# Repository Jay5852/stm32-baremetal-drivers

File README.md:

# STM32 Bare-Metal Driver Development & Custom PCB Design

## 📌 Overview

This project demonstrates low-level embedded systems development using STM32 microcontrollers.

## 🚀 Features

- UART Driver (Polling, Interrupt, DMA)
- ADC Driver (Polling + DMA)
- Timer-triggered ADC sampling
- Custom STM32 PCB Design

## 🧠 Key Concepts

- Register-level programming
- RCC configuration
- Interrupt handling (NVIC)
- DMA optimization
- Power design and decoupling

## 🛠 Tools Used

- STM32CubeIDE
- KiCad
- Git & GitHub

## 📌 Author

Jay Dukare

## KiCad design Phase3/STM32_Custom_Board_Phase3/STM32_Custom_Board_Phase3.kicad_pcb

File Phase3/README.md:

# STM32 Custom Board Project

## Overview
A custom STM32F401 breakout board designed for student lab use.

## Contents
- /gerber_files: Manufacturing data (Gerber + Drill).
- /layout_pdfs: PDF visual guides.
- schematic.pdf: Circuit diagram.

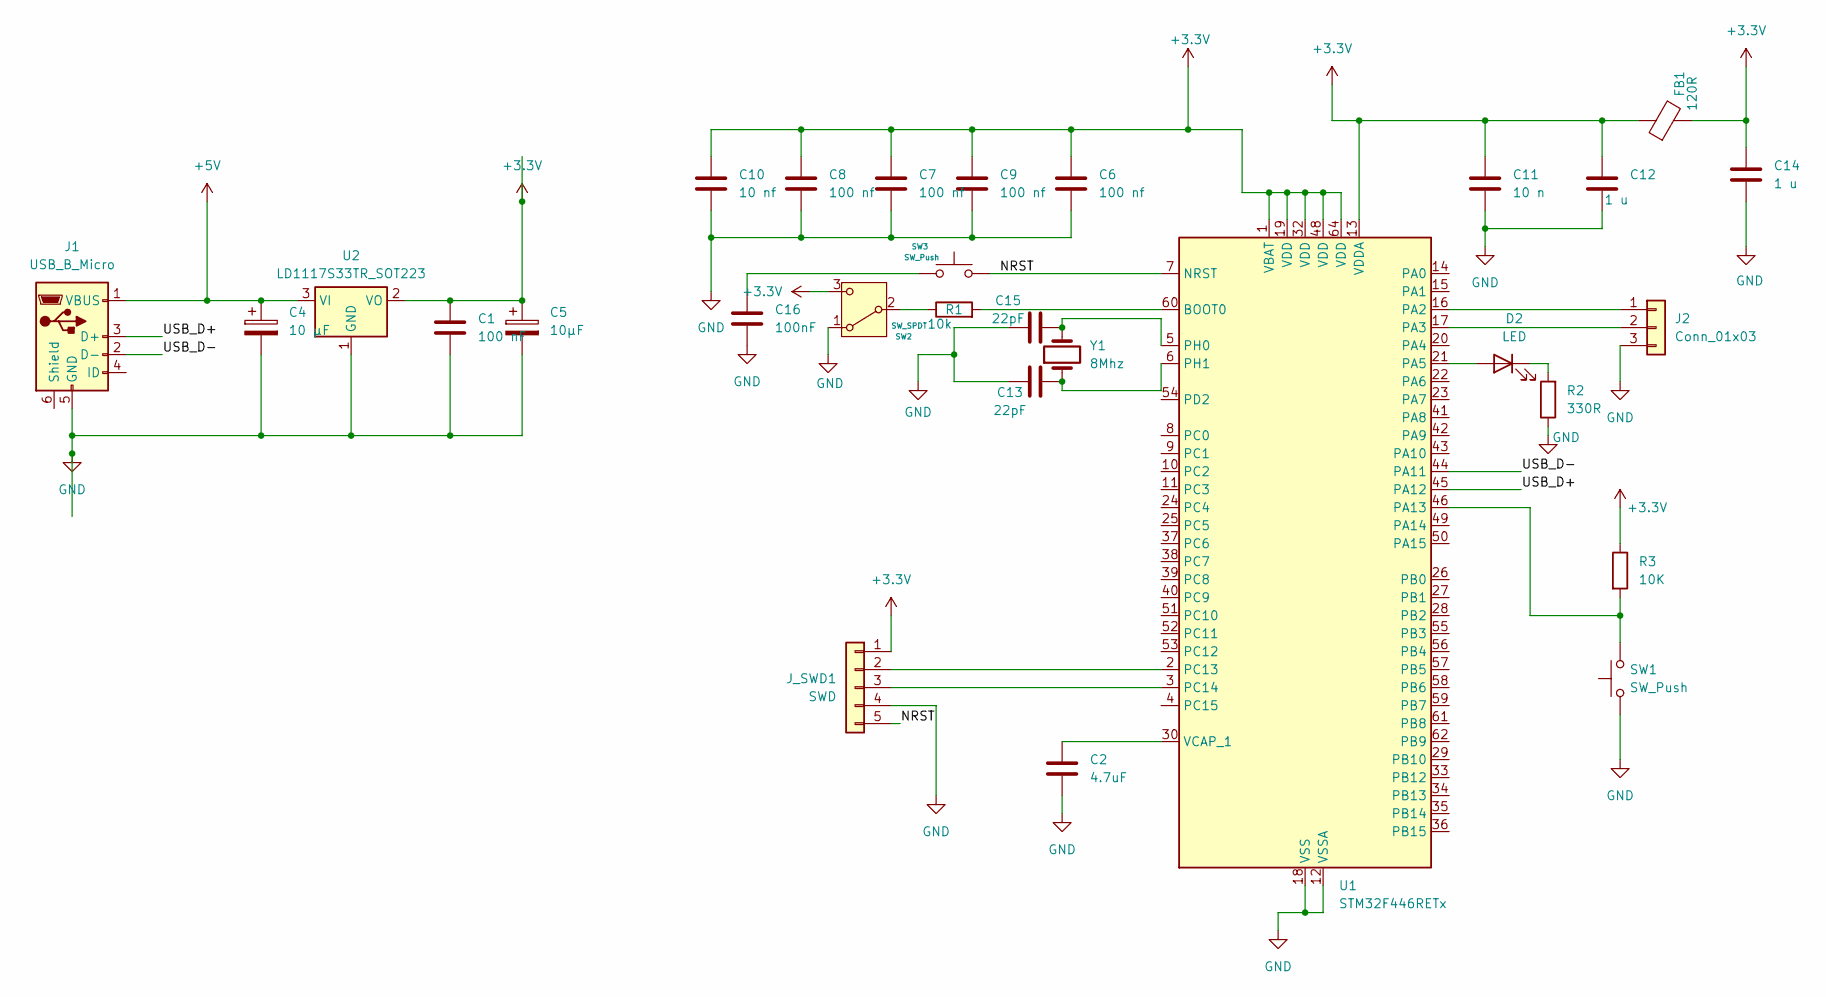
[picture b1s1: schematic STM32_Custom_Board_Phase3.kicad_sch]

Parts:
C1: 100 nF; C_0603_1608Metric
C2: 4.7uF; C_0603_1608Metric
C4: 10 µF; C_0603_1608Metric
C5: 10µF; C_0603_1608Metric
C6, C7, C8, C9: 100 nf; C_0603_1608Metric
C10: 10 nf; C_0603_1608Metric
C11: 10 n; C_0603_1608Metric
C12, C14: 1 u; C_0603_1608Metric
C13, C15: 22pF; C_0603_1608Metric
C16: 100nF; C_0603_1608Metric
D2: LED; LED_0603_1608Metric
FB1: 120R; L_0603_1608Metric
J1: USB_B_Micro; USB_Micro-B_Molex-105017-0001
J2: Conn_01x03; PinHeader_1x03_P2.54mm_Vertical
J_SWD1: SWD; PinHeader_1x05_P2.54mm_Vertical
R1: 10k; R_0603_1608Metric
R2: 330R; R_0603_1608Metric
R3: 10K; R_0603_1608Metric
SW1, SW3: SW_Push; SW_Push_1TS009xxxx-xxxx-xxxx_6x6x5mm
SW2: SW_SPDT; SW_SPDT_PCM12
U1: STM32F446RETx; LQFP-64_10x10mm_P0.5mm
U2: LD1117S33TR_SOT223; SOT-223-3_TabPin2
Y1: 8Mhz; Crystal_SMD_5032-2Pin_5.0x3.2mm

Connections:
+3.3V: C1.1, C5.1, C6.1, C7.1, C8.1, C9.1, C10.1, C11.1, C12.1, C14.1, FB1.1, FB1.2, J_SWD1.1, R3.1, SW2.3 (C), U1.1 (VBAT), U1.13 (VDDA), U1.19 (VDD), U1.32 (VDD), U1.48 (VDD), U1.64 (VDD), U2.2 (VO)
+5V: C4.1, J1.1 (VBUS), U2.3 (VI)
/NRST: J_SWD1.5, SW3.2, U1.7 (NRST)
/USB_D+: J1.3 (D+), U1.45 (PA12)
/USB_D-: J1.2 (D-), U1.44 (PA11)
GND: C1.2, C2.2, C4.2, C5.2, C6.2, C7.2, C8.2, C9.2, C10.2, C11.2, C12.2, C13.1, C14.2, C15.1, C16.2, J1.5 (GND), J2.3, J_SWD1.4, R2.1, SW1.1, SW2.1 (A), U1.12 (VSSA), U1.18 (VSS), U1.31 (VSS), U1.47 (VSS), U1.63 (VSS), U2.1 (GND)
unnamed: C16.1, SW3.1
unnamed: D2.2 (A), U1.21 (PA5)
unnamed: D2.1 (K), R2.2
unnamed: J2.1, U1.16 (PA2)
unnamed: J2.2, U1.17 (PA3)
unnamed: J_SWD1.2, U1.2 (PC13)
unnamed: J_SWD1.3, U1.3 (PC14)
unnamed: R1.1, SW2.2 (B)
unnamed: R1.2, U1.60 (BOOT0)
unnamed: R3.2, SW1.2, U1.46 (PA13)
unnamed: C15.2, U1.5 (PH0), Y1.2
unnamed: C13.2, U1.6 (PH1), Y1.1
unnamed: C2.1, U1.30 (VCAP_1)

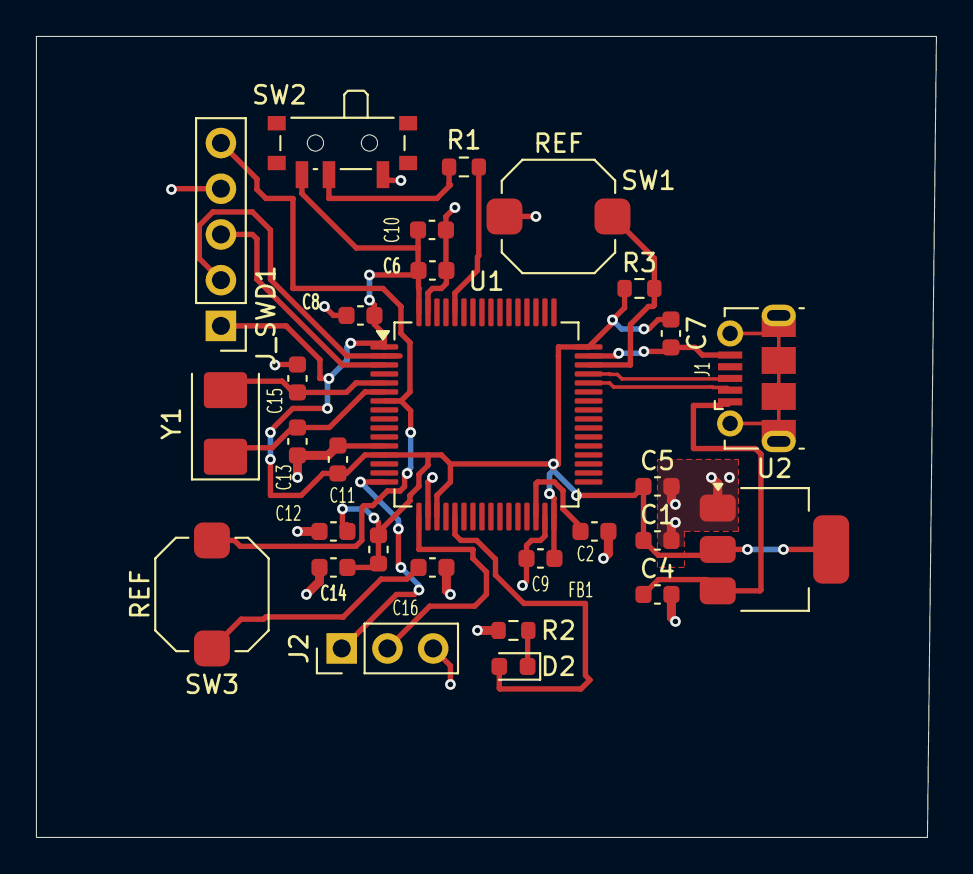
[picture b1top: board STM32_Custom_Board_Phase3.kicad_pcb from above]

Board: 2 copper layers, 50.0 x 44.5 mm, 29 parts (0 on the bottom side), 19 nets.

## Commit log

2026-03-25 Initial commit: STM32 bare-metal drivers and PCB design
2026-03-25 Track demo video with Git LFS
